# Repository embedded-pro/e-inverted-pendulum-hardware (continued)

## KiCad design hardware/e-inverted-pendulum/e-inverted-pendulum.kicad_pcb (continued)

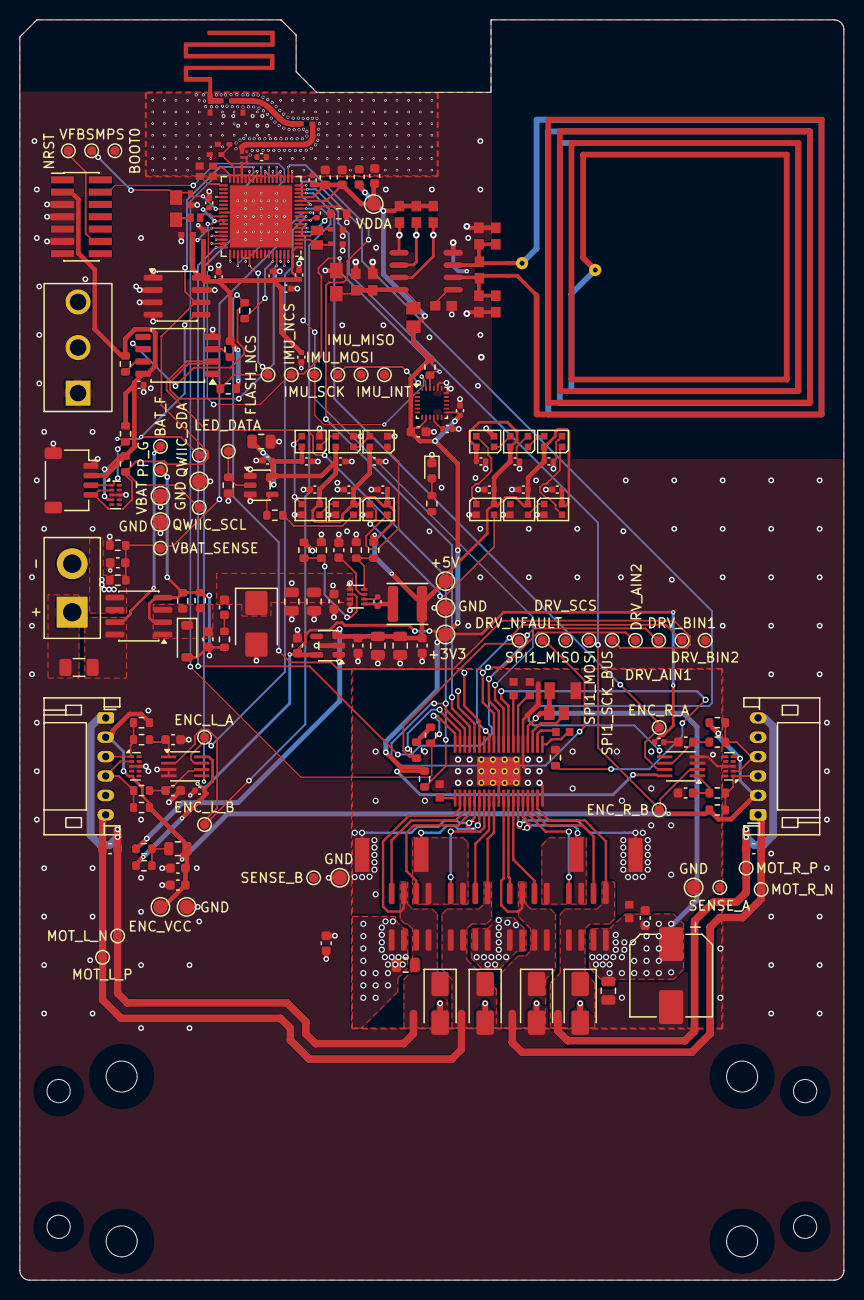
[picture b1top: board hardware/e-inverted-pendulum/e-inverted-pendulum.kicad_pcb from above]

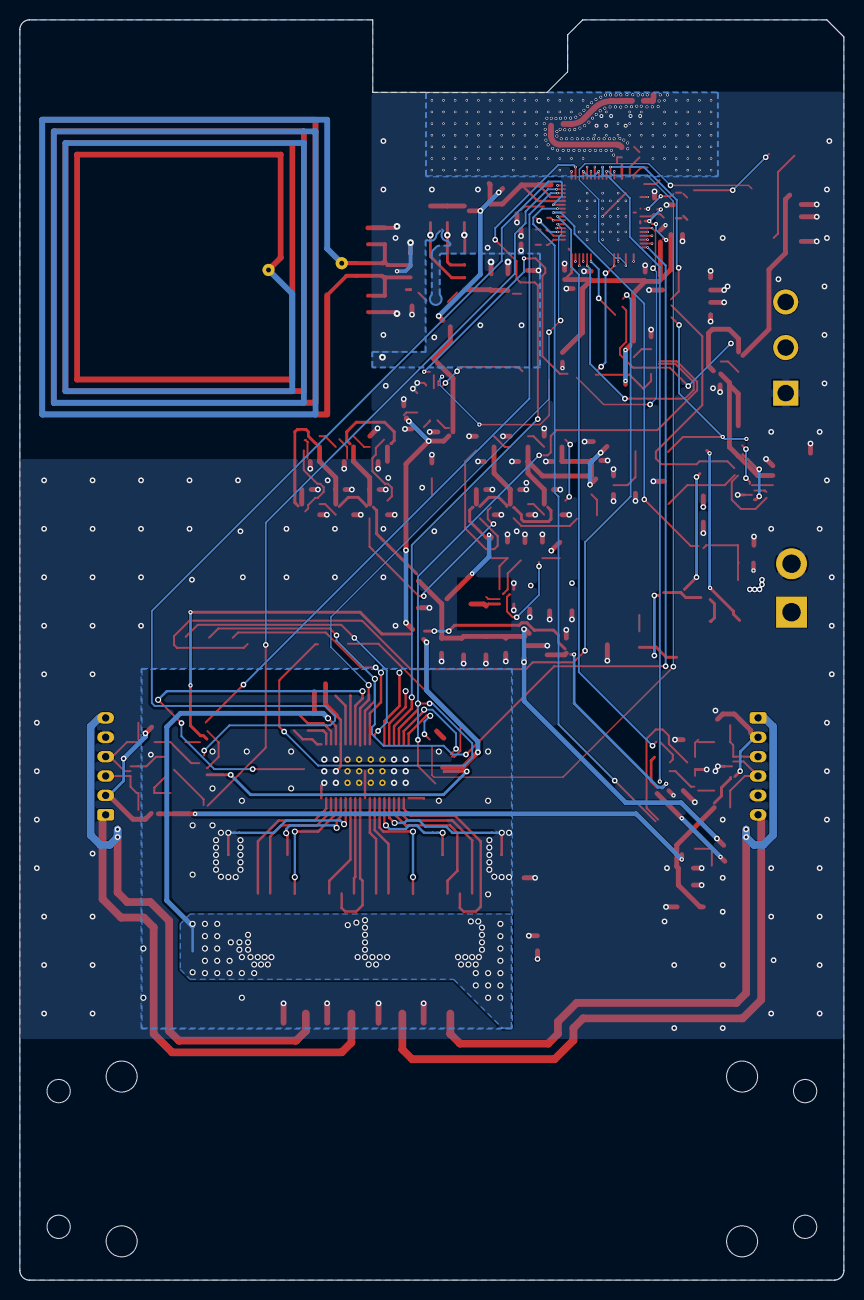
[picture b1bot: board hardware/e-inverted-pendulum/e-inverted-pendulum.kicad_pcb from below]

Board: 4 copper layers, 85.0 x 130.0 mm, 245 parts (4 on the bottom side), 119 nets.

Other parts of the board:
MB1, MB2, MB3, MB4: bracket M3; MountingHole_M3_NPTH_KeepOut7mm
MB5, MB6, MB7, MB8: bracket M2; MountingHole_M2_NPTH_KeepOut5.5mm
MC1, MC2, MC3, MC4: battery cradle; MountingHole_M3_NPTH_KeepOut7mm
MH1: bumper; MountingHole_M3_NPTH_KeepOut7mm
MH2: bumper (nylon); MountingHole_M3_NPTH_KeepOut7mm

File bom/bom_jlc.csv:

Comment,Designator,Footprint,LCSC Part #
MLT-8530,BZ801,Buzzer_MLT-8530_8.5x8.5mm,C94599
47nF 50V,"C101,C205",C_0603_1608Metric,C1622
1uF 50V,"C102,C209,C311,C313,C509,C512",C_0603_1608Metric,C15849
100nF 50V,"C103,C203,C208,C503,C506,C510,C602,C801",C_0603_1608Metric,C14663
10uF 25V,"C201,C202,C502,C505",C_0805_2012Metric,C15850
100nF 16V,"C204,C301,C302,C303,C304,C305,C307,C312,C317,C511,C606,C610,C701,C703,C704,C802,C803",C_0402_1005Metric,C1525
22uF 25V,"C206,C207",C_0805_2012Metric,C45783
2.2uF 25V,C210,C_0603_1608Metric,C23630
4.7uF 10V,"C306,C309,C314",C_0402_1005Metric,C23733
100pF 50V,C308,C_0402_1005Metric,C26409
10nF 50V,"C310,C508,C702",C_0603_1608Metric,C1589
6.8pF 50V,"C315,C316",C_0402_1005Metric,C318598
220u 35V,C507,CP_Elec_8x10,C178562
1nF 50V,C513,C_0402_1005Metric,C307441
10uF 10V,C601,C_0603_1608Metric,C19702
1nF 50V,"C604,C605,C608,C609",C_0603_1608Metric,C1588
BZT52C15,D101,D_SOD-123,C2104
SMBJ15A,D102,D_SMB,C83846
SS34,"D501,D502,D503,D504",D_SMA,C8678
green,D801,LED_0603_1608Metric,C12624
red,D802,LED_0603_1608Metric,C2286
1N4148WS,D803,D_SOD-323,C2128
4A fast,F101,Fuse_1206_3216Metric,C2937379
PTC 100mA,F601,Fuse_0805_2012Metric,C20975
BLM18PG221SN1D,FB301,L_0603_1608Metric,C80165
MLPF-WB55-01E3,FL401,ST_MLPF-WB55-01E3,C2651048
XT30 battery,J101,AMASS_XT30UPB-F_1x02_P5.00mm_Vertical,C108769
STDC14,J301,PinHeader_2x07_P1.27mm_Vertical_SMD,C5307809
"Motor left,Motor right","J601,J602",JST_PH_S6B-PH-K_1x06_P2.00mm_Horizontal,C157920
Qwiic,J801,JST_SH_SM04B-SRSS-TB_1x04-1MP_P1.00mm_Horizontal,C160404
4.7uH,L201,L_Sunlord_SWPA4030S,C57269
10uH,L301,L_0805_2012Metric,C162582
10nH,L302,L_0402_1005Metric,C77103
AO4805,Q101,SOIC-8_3.9x4.9mm_P1.27mm,C3040596
CSD88537ND,"Q501,Q502,Q503,Q504",SOIC-8_3.9x4.9mm_P1.27mm,C117439
MMBT3904,Q801,SOT-23,C20526
100k,"R101,R102,R104",R_0603_1608Metric,C25803
1k,"R103,R303",R_0603_1608Metric,C21190
27k,R105,R_0603_1608Metric,C22967
240k,R201,R_0603_1608Metric,C4197
36k,R202,R_0603_1608Metric,C23147
52.3k,R203,R_0603_1608Metric,C23198
10k,"R204,R302,R515,R516,R518,R701,R702,R703,R704,R803,R807,R810",R_0603_1608Metric,C25804
33,"R301,R805",R_0603_1608Metric,C23140
0,R401,R_0402_1005Metric,C17168
0,"R501,R502,R503,R504,R505,R506,R507,R508,R510,R511,R513,R514,R601",R_0603_1608Metric,C21189
50m,"R509,R512",R_1206_3216Metric,C601102
2.2k,"R517,R808,R809",R_0603_1608Metric,C4190
100,"R604,R606,R608,R610,R804",R_0603_1608Metric,C22775
470,"R801,R806",R_0603_1608Metric,C23179
680,R802,R_0603_1608Metric,C23228
SS-12D10L5,SW101,SW_Slide_SPDT_SS-12D10L5_P4.70mm,C319012
"BOOT0,USER","SW301,SW801",SW_Push_TS-1187A_5.1x5.1mm,C318884
TPS62933F,U201,SOT-583-8,C5219272
TLV75533P,U202,SOT-23-5,C404027
STM32WB55RGV6,U301,QFN-68-1EP_8x8mm_P0.4mm_EP6.4x6.4mm,C401505
DRV8711,U501,HTSSOP-38-1EP_4.4x9.7mm_P0.5mm_EP2.74x4.75mm_ThermalVias,C60013
TPD4E05U06DQAR,"U601,U603,U801",USON-10_2.5x1.0mm_P0.5mm,C138714
SN74LVC3G17DCTR,"U602,U604",SSOP-8_2.95x2.8mm_P0.65mm,C18213
MPU-6500,U701,InvenSense_QFN-24_3x3mm_P0.4mm,C50278
W25Q16JVSSIQ,U702,SOIC-8_5.3x5.3mm_P1.27mm,C131025
M24C64-RMN6TP,U802,SOIC-8_3.9x4.9mm_P1.27mm,C79988
ST25DV04KC-IE8S3,U803,SOIC-8_3.9x4.9mm_P1.27mm,C5221752
32MHz,Y301,Crystal_SMD_2016-4Pin_2.0x1.6mm,C5441424
32.768kHz,Y302,Crystal_SMD_3215-2Pin_3.2x1.5mm,C156244

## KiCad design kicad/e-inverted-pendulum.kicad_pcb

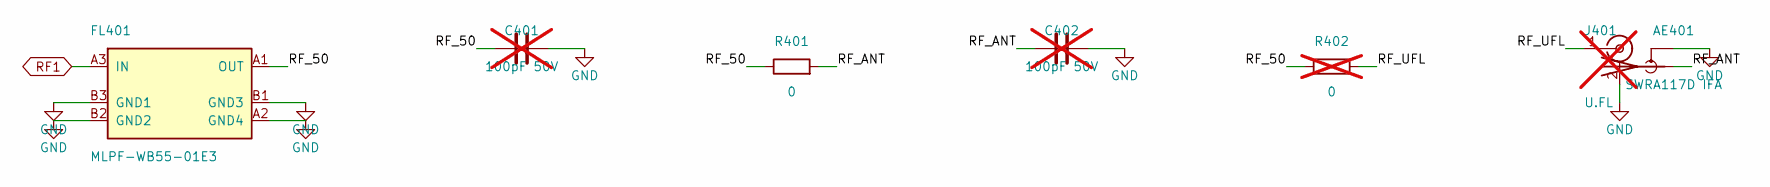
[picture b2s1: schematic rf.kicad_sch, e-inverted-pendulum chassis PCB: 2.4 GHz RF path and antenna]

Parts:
AE401: SWRA117D IFA; Texas_SWRA117D_2.4GHz_Left
C401, C402: 100pF 50V; C_0402_1005Metric; MPN CL05C101JB5NNNC; LCSC C26409; not fitted
FL401: MLPF-WB55-01E3; ST_MLPF-WB55-01E3; MPN MLPF-WB55-01E3; LCSC C2651048
J401: U.FL; U.FL_Hirose_U.FL-R-SMT-1_Vertical; MPN BWU.FL-IPEX1; LCSC C5137195; not fitted
R401: 0; R_0402_1005Metric; MPN 0402WGF0000TCE; LCSC C17168
R402: 0; R_0402_1005Metric; MPN 0402WGF0000TCE; LCSC C17168; not fitted

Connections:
/4 2.4 GHz RF path and antenna/RF_50: C401.1, FL401.A1 (OUT), R401.1, R402.1
/4 2.4 GHz RF path and antenna/RF_ANT: AE401.1 (A), C402.1, R401.2
/4 2.4 GHz RF path and antenna/RF_UFL: J401.1 (In), R402.2
GND: AE401.2 (Shield), C401.2, C402.2, FL401.A2 (GND4), FL401.B1 (GND3), FL401.B2 (GND2), FL401.B3 (GND1), J401.2 (Ext); also elsewhere on the board
RF1: FL401.A3 (IN); also elsewhere on the board

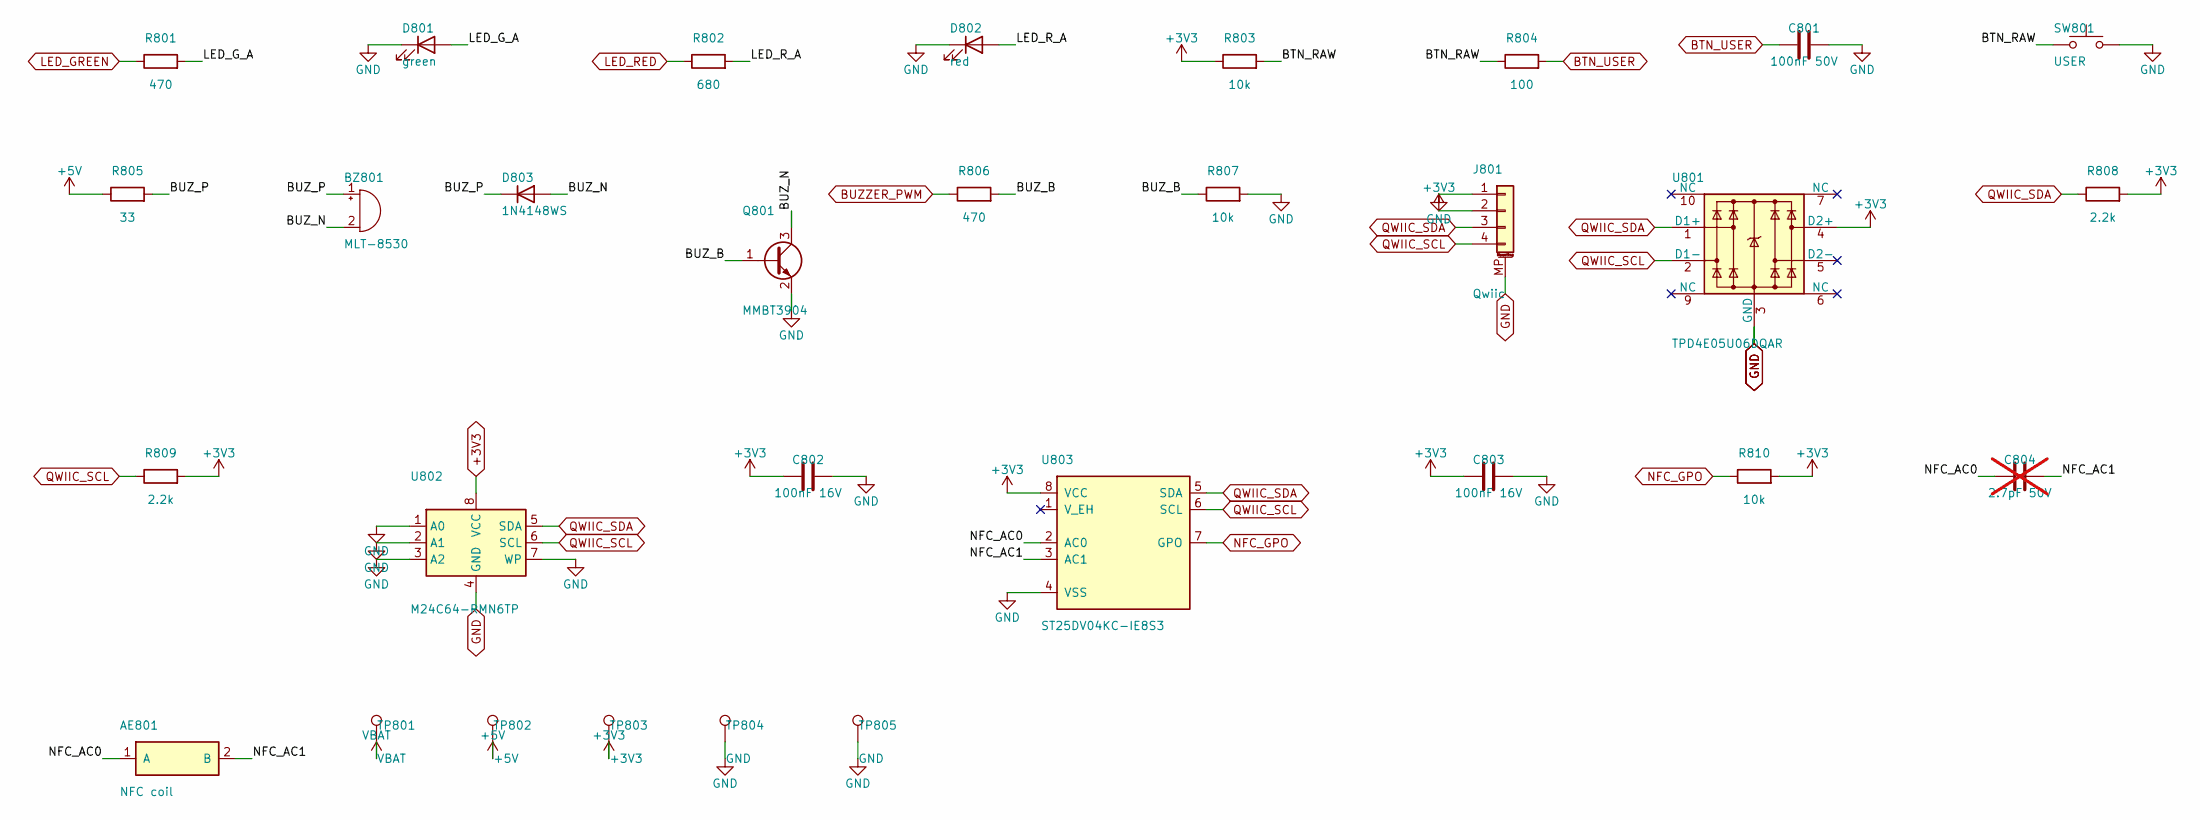
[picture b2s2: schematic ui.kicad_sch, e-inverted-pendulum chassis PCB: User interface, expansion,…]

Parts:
AE801: NFC coil; NFC_Coil_25x21mm
BZ801: MLT-8530; Buzzer_MLT-8530_8.5x8.5mm; MPN MLT-8530; LCSC C94599
C801: 100nF 50V; C_0603_1608Metric; MPN CC0603KRX7R9BB104; LCSC C14663
C802, C803: 100nF 16V; C_0402_1005Metric; MPN CL05B104KO5NNNC; LCSC C1525
C804: 2.7pF 50V; C_0402_1005Metric; MPN CL05C2R7CB5NNNC; LCSC C318593; not fitted
D801: green; LED_0603_1608Metric; MPN KT-0603G; LCSC C12624
D802: red; LED_0603_1608Metric; MPN KT-0603R; LCSC C2286
D803: 1N4148WS; D_SOD-323; MPN 1N4148WS; LCSC C2128
J801: Qwiic; JST_SH_SM04B-SRSS-TB_1x04-1MP_P1.00mm_Horizontal; MPN SM04B-SRSS-TB(LF)(SN); LCSC C160404
Q801: MMBT3904; SOT-23; MPN MMBT3904; LCSC C20526
R801, R806: 470; R_0603_1608Metric; MPN 0603WAF4700T5E; LCSC C23179
R802: 680; R_0603_1608Metric; MPN 0603WAF6800T5E; LCSC C23228
R803, R807, R810: 10k; R_0603_1608Metric; MPN 0603WAF1002T5E; LCSC C25804
R804: 100; R_0603_1608Metric; MPN 0603WAF1000T5E; LCSC C22775
R805: 33; R_0603_1608Metric; MPN 0603WAF330JT5E; LCSC C23140
R808, R809: 2.2k; R_0603_1608Metric; MPN 0603WAF2201T5E; LCSC C4190
SW801: USER; SW_Push_TS-1187A_5.1x5.1mm; MPN TS-1187A-B-A-B; LCSC C318884
TP801: VBAT; TestPoint_Pad_D1.0mm
TP802: +5V; TestPoint_Pad_D1.0mm
TP803: +3V3; TestPoint_Pad_D1.0mm
TP804, TP805: GND; TestPoint_Pad_D1.0mm
U801: TPD4E05U06DQAR; USON-10_2.5x1.0mm_P0.5mm; MPN TPD4E05U06DQAR; LCSC C138714
U802: M24C64-RMN6TP; SOIC-8_3.9x4.9mm_P1.27mm; MPN M24C64-RMN6TP; LCSC C79988
U803: ST25DV04KC-IE8S3; SOIC-8_3.9x4.9mm_P1.27mm; MPN ST25DV04KC-IE8S3; LCSC C5221752

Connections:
+3V3: C802.1, C803.1, J801.2, R803.1, R808.2, R809.2, R810.2, TP803.1, U801.4 (D2+), U802.8 (VCC), U803.8 (VCC); also elsewhere on the board
+5V: R805.1, TP802.1; also elsewhere on the board
/8 User interface, expansion, test points/BTN_RAW: R803.2, R804.1, SW801.1
/8 User interface, expansion, test points/BUZ_B: Q801.1 (B), R806.2, R807.1
/8 User interface, expansion, test points/BUZ_N: BZ801.2 (-), D803.2 (A), Q801.3 (C)
/8 User interface, expansion, test points/BUZ_P: BZ801.1 (+), D803.1 (K), R805.2
/8 User interface, expansion, test points/LED_G_A: D801.2 (A), R801.2
/8 User interface, expansion, test points/LED_R_A: D802.2 (A), R802.2
/8 User interface, expansion, test points/NFC_AC0: AE801.1 (A), C804.1, U803.2 (AC0)
/8 User interface, expansion, test points/NFC_AC1: AE801.2 (B), C804.2, U803.3 (AC1)
BTN_USER: C801.1, R804.2; also elsewhere on the board
BUZZER_PWM: R806.1; also elsewhere on the board
GND: C801.2, C802.2, C803.2, D801.1 (K), D802.1 (K), J801.1, J801.MP (MountPin), Q801.2 (E), R807.2, SW801.2, TP804.1, TP805.1, U801.3 (GND), U801.8 (GND), U802.1 (A0), U802.2 (A1), U802.3 (A2), U802.4 (GND), U802.7 (WP), U803.4 (VSS); also elsewhere on the board
LED_GREEN: R801.1; also elsewhere on the board
LED_RED: R802.1; also elsewhere on the board
NFC_GPO: R810.1, U803.7 (GPO); also elsewhere on the board
QWIIC_SCL: J801.4, R809.1, U801.2 (D1-), U802.6 (SCL), U803.6 (SCL); also elsewhere on the board
QWIIC_SDA: J801.3, R808.1, U801.1 (D1+), U802.5 (SDA), U803.5 (SDA); also elsewhere on the board
VBAT: TP801.1; also elsewhere on the board

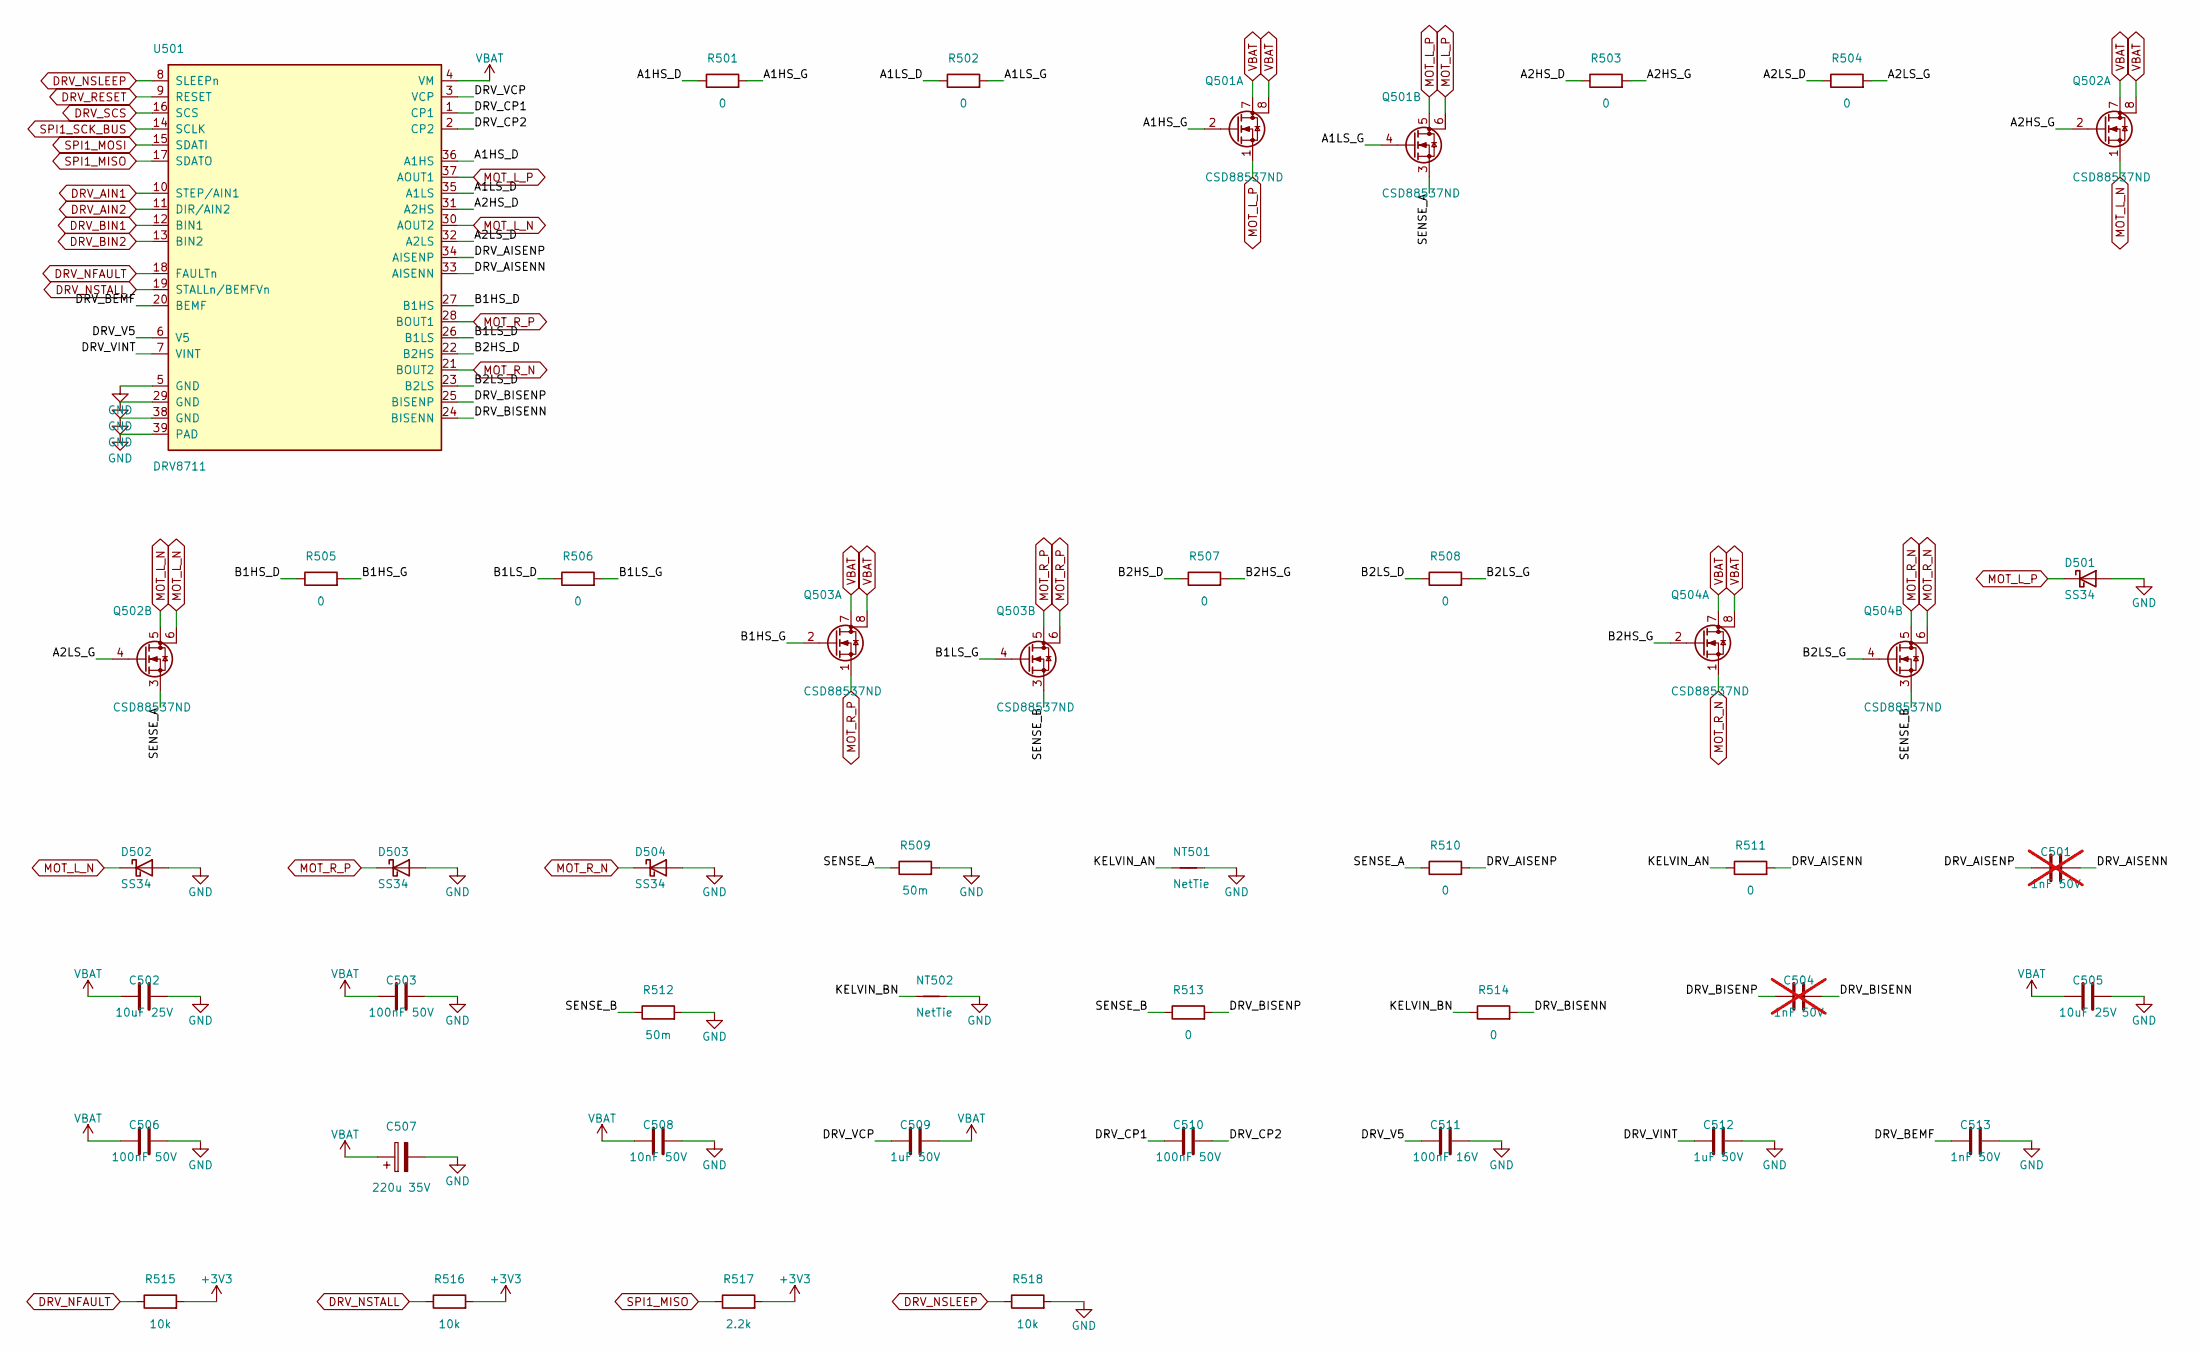
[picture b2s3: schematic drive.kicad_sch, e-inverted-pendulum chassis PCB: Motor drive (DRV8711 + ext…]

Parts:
C501, C504: 1nF 50V; C_0402_1005Metric; MPN CL05C102JB5NNNC; LCSC C307441; not fitted
C502, C505: 10uF 25V; C_0805_2012Metric; MPN CL21A106KAYNNNE; LCSC C15850
C503, C506, C510: 100nF 50V; C_0603_1608Metric; MPN CC0603KRX7R9BB104; LCSC C14663
C507: 220u 35V; CP_Elec_8x10; MPN EEEFK1V221P; LCSC C178562
C508: 10nF 50V; C_0603_1608Metric; MPN CL10B103KB8NNNC; LCSC C1589
C509, C512: 1uF 50V; C_0603_1608Metric; MPN CL10A105KB8NNNC; LCSC C15849
C511: 100nF 16V; C_0402_1005Metric; MPN CL05B104KO5NNNC; LCSC C1525
C513: 1nF 50V; C_0402_1005Metric; MPN CL05C102JB5NNNC; LCSC C307441
D501, D502, D503, D504: SS34; D_SMA; MPN SS34; LCSC C8678
NT501, NT502: NetTie; NetTie-2_SMD_Pad0.5mm
Q501, Q502, Q503, Q504: CSD88537ND; SOIC-8_3.9x4.9mm_P1.27mm; MPN CSD88537ND; LCSC C117439
R501, R502, R503, R504, R505, R506, R507, R508, R510, R511, R513, R514: 0; R_0603_1608Metric; MPN 0603WAF0000T5E; LCSC C21189
R509, R512: 50m; R_1206_3216Metric; MPN HoLR1206-1W-50mR-1%-75ppm; LCSC C601102
R515, R516, R518: 10k; R_0603_1608Metric; MPN 0603WAF1002T5E; LCSC C25804
R517: 2.2k; R_0603_1608Metric; MPN 0603WAF2201T5E; LCSC C4190
U501: DRV8711; HTSSOP-38-1EP_4.4x9.7mm_P0.5mm_EP2.74x4.75mm_ThermalVias; MPN DRV8711DCPR; LCSC C60013

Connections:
+3V3: R515.2, R516.2, R517.2; also elsewhere on the board
/5 Motor drive (DRV8711 + external FETs)/A1HS_D: R501.1, U501.36 (A1HS)
/5 Motor drive (DRV8711 + external FETs)/A1HS_G: Q501.2 (G), R501.2
/5 Motor drive (DRV8711 + external FETs)/A1LS_D: R502.1, U501.35 (A1LS)
/5 Motor drive (DRV8711 + external FETs)/A1LS_G: Q501.4 (G), R502.2
/5 Motor drive (DRV8711 + external FETs)/A2HS_D: R503.1, U501.31 (A2HS)
/5 Motor drive (DRV8711 + external FETs)/A2HS_G: Q502.2 (G), R503.2
/5 Motor drive (DRV8711 + external FETs)/A2LS_D: R504.1, U501.32 (A2LS)
/5 Motor drive (DRV8711 + external FETs)/A2LS_G: Q502.4 (G), R504.2
/5 Motor drive (DRV8711 + external FETs)/B1HS_D: R505.1, U501.27 (B1HS)
/5 Motor drive (DRV8711 + external FETs)/B1HS_G: Q503.2 (G), R505.2
/5 Motor drive (DRV8711 + external FETs)/B1LS_D: R506.1, U501.26 (B1LS)
/5 Motor drive (DRV8711 + external FETs)/B1LS_G: Q503.4 (G), R506.2
/5 Motor drive (DRV8711 + external FETs)/B2HS_D: R507.1, U501.22 (B2HS)
/5 Motor drive (DRV8711 + external FETs)/B2HS_G: Q504.2 (G), R507.2
/5 Motor drive (DRV8711 + external FETs)/B2LS_D: R508.1, U501.23 (B2LS)
/5 Motor drive (DRV8711 + external FETs)/B2LS_G: Q504.4 (G), R508.2
/5 Motor drive (DRV8711 + external FETs)/DRV_AISENN: C501.2, R511.2, U501.33 (AISENN)
/5 Motor drive (DRV8711 + external FETs)/DRV_AISENP: C501.1, R510.2, U501.34 (AISENP)
/5 Motor drive (DRV8711 + external FETs)/DRV_BEMF: C513.1, U501.20 (BEMF)
/5 Motor drive (DRV8711 + external FETs)/DRV_BISENN: C504.2, R514.2, U501.24 (BISENN)
/5 Motor drive (DRV8711 + external FETs)/DRV_BISENP: C504.1, R513.2, U501.25 (BISENP)
/5 Motor drive (DRV8711 + external FETs)/DRV_CP1: C510.1, U501.1 (CP1)
/5 Motor drive (DRV8711 + external FETs)/DRV_CP2: C510.2, U501.2 (CP2)
/5 Motor drive (DRV8711 + external FETs)/DRV_V5: C511.1, U501.6 (V5)
/5 Motor drive (DRV8711 + external FETs)/DRV_VCP: C509.1, U501.3 (VCP)
/5 Motor drive (DRV8711 + external FETs)/DRV_VINT: C512.1, U501.7 (VINT)
/5 Motor drive (DRV8711 + external FETs)/KELVIN_AN: NT501.1, R511.1
/5 Motor drive (DRV8711 + external FETs)/KELVIN_BN: NT502.1, R514.1
/5 Motor drive (DRV8711 + external FETs)/SENSE_A: Q501.3 (S), Q502.3 (S), R509.1, R510.1
/5 Motor drive (DRV8711 + external FETs)/SENSE_B: Q503.3 (S), Q504.3 (S), R512.1, R513.1
DRV_AIN1: U501.10 (STEP/AIN1); also elsewhere on the board
DRV_AIN2: U501.11 (DIR/AIN2); also elsewhere on the board
DRV_BIN1: U501.12 (BIN1); also elsewhere on the board
DRV_BIN2: U501.13 (BIN2); also elsewhere on the board
DRV_NFAULT: R515.1, U501.18 (FAULTn); also elsewhere on the board
DRV_NSLEEP: R518.1, U501.8 (SLEEPn); also elsewhere on the board
DRV_NSTALL: R516.1, U501.19 (STALLn/BEMFVn); also elsewhere on the board
DRV_RESET: U501.9 (RESET); also elsewhere on the board
DRV_SCS: U501.16 (SCS); also elsewhere on the board
GND: C502.2, C503.2, C505.2, C506.2, C507.2, C508.2, C511.2, C512.2, C513.2, D501.2 (A), D502.2 (A), D503.2 (A), D504.2 (A), NT501.2, NT502.2, R509.2, R512.2, R518.2, U501.5 (GND), U501.29 (GND), U501.38 (GND), U501.39 (PAD); also elsewhere on the board
MOT_L_N: D502.1 (K), Q502.1 (S), Q502.5 (D), Q502.6 (D), U501.30 (AOUT2); also elsewhere on the board
MOT_L_P: D501.1 (K), Q501.1 (S), Q501.5 (D), Q501.6 (D), U501.37 (AOUT1); also elsewhere on the board
MOT_R_N: D504.1 (K), Q504.1 (S), Q504.5 (D), Q504.6 (D), U501.21 (BOUT2); also elsewhere on the board
MOT_R_P: D503.1 (K), Q503.1 (S), Q503.5 (D), Q503.6 (D), U501.28 (BOUT1); also elsewhere on the board
SPI1_MISO: R517.1, U501.17 (SDATO); also elsewhere on the board
SPI1_MOSI: U501.15 (SDATI); also elsewhere on the board
SPI1_SCK_BUS: U501.14 (SCLK); also elsewhere on the board
VBAT: C502.1, C503.1, C505.1, C506.1, C507.1, C508.1, C509.2, Q501.7 (D), Q501.8 (D), Q502.7 (D), Q502.8 (D), Q503.7 (D), Q503.8 (D), Q504.7 (D), Q504.8 (D), U501.4 (VM); also elsewhere on the board

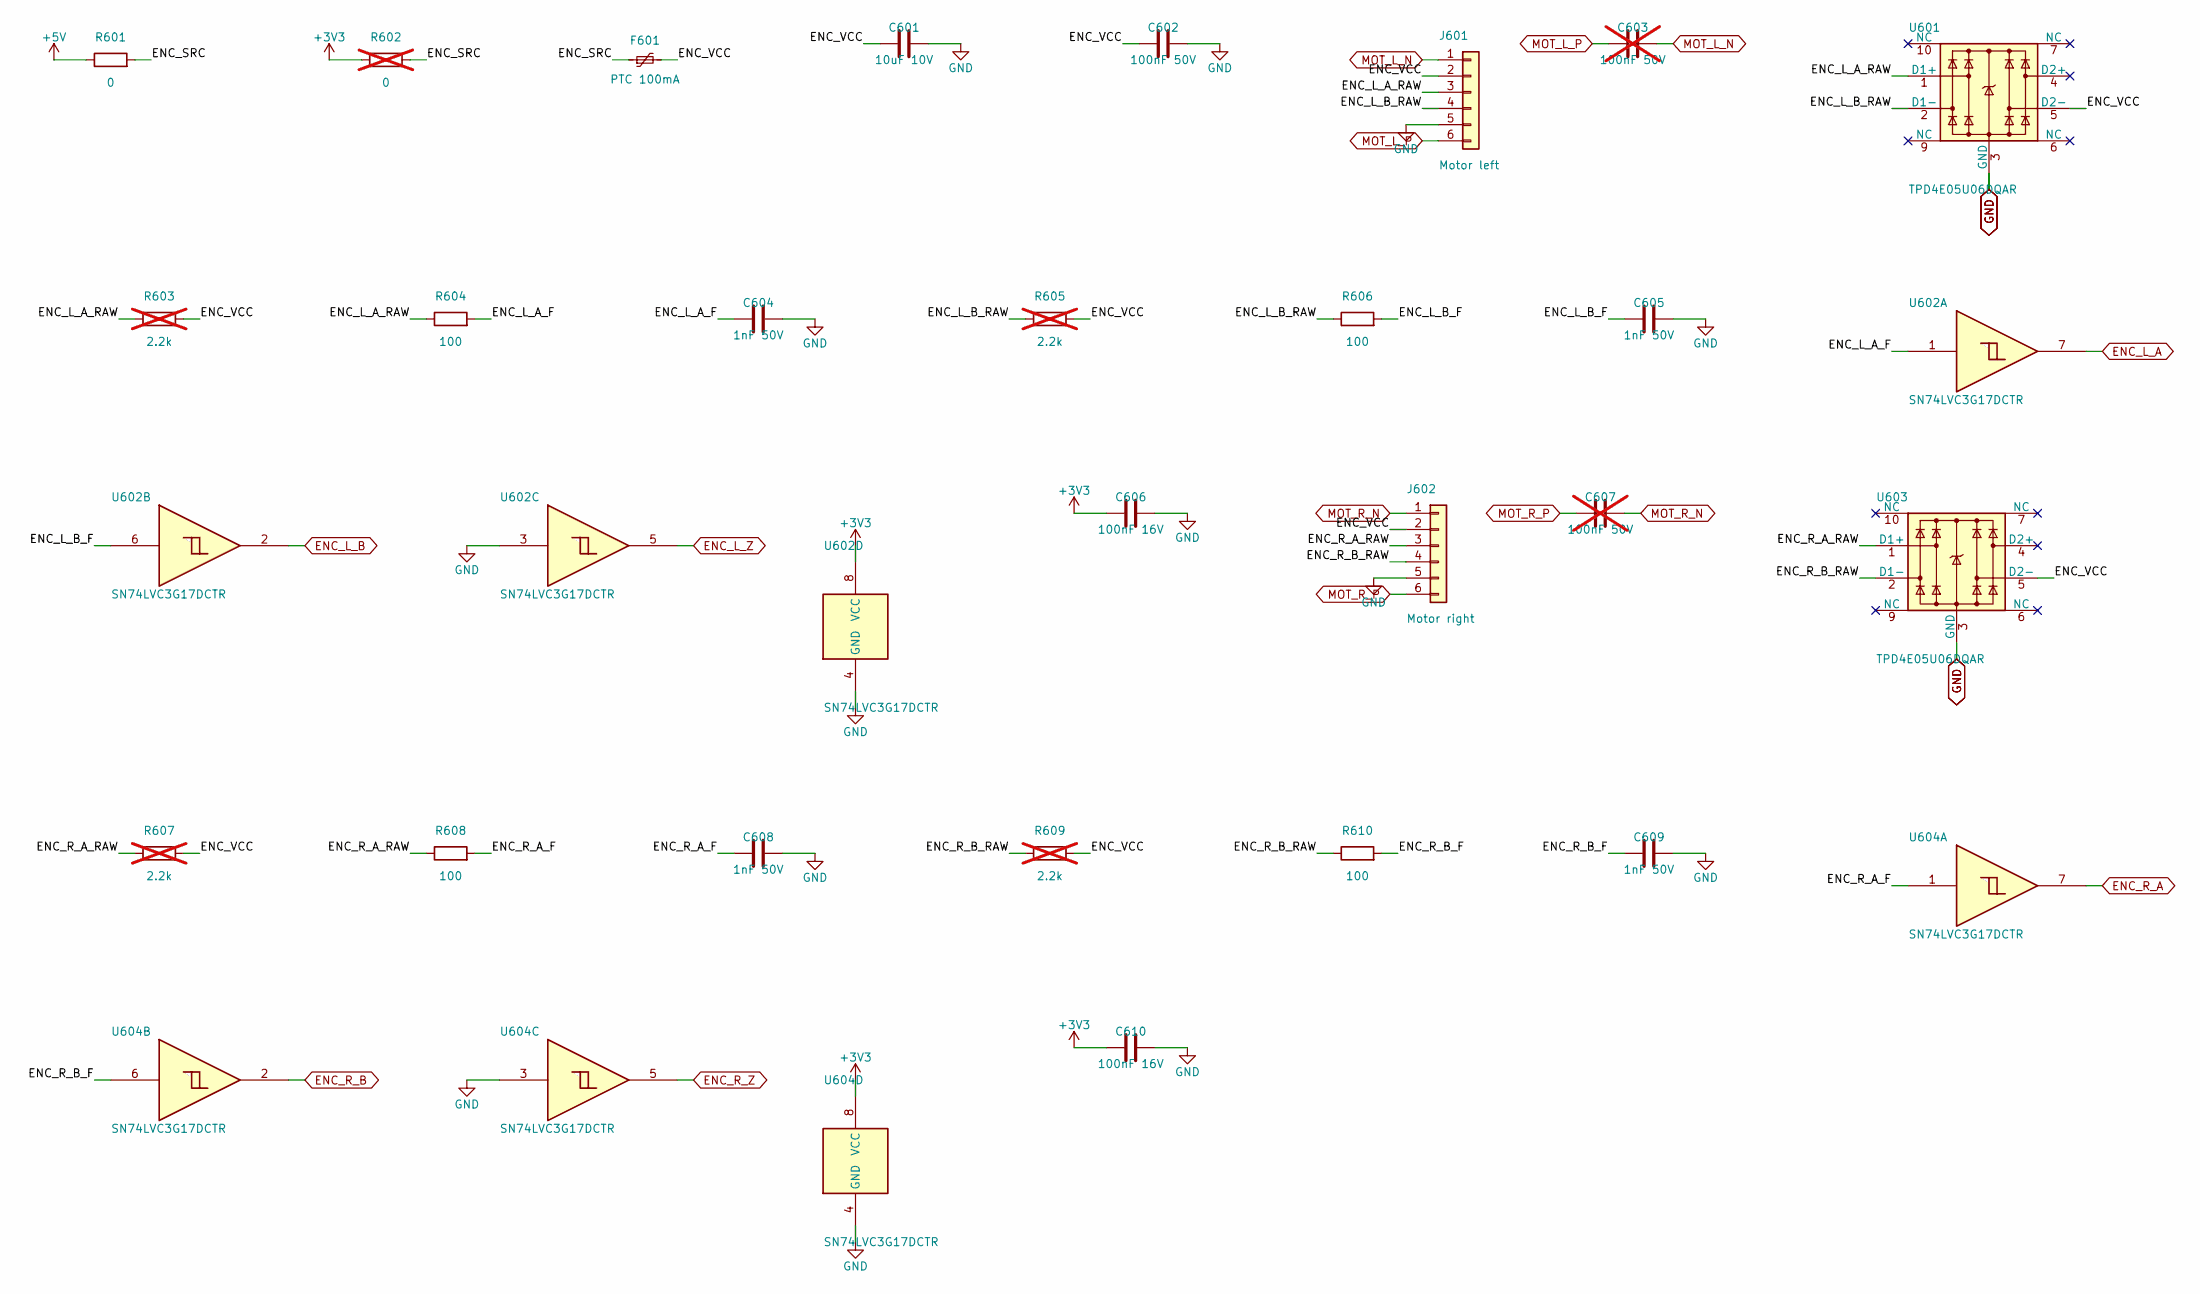
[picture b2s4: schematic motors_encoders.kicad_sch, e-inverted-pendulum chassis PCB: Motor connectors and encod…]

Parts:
C601: 10uF 10V; C_0603_1608Metric; MPN CL10A106KP8NNNC; LCSC C19702
C602: 100nF 50V; C_0603_1608Metric; MPN CC0603KRX7R9BB104; LCSC C14663
C603, C607: 100nF 50V; C_0603_1608Metric; MPN CC0603KRX7R9BB104; LCSC C14663; not fitted
C604, C605, C608, C609: 1nF 50V; C_0603_1608Metric; MPN CL10B102KB8NNNC; LCSC C1588
C606, C610: 100nF 16V; C_0402_1005Metric; MPN CL05B104KO5NNNC; LCSC C1525
F601: PTC 100mA; Fuse_0805_2012Metric; MPN SMD0805P010TF; LCSC C20975
J601: Motor left; JST_PH_S6B-PH-K_1x06_P2.00mm_Horizontal; MPN S6B-PH-K-S(LF)(SN); LCSC C157920
J602: Motor right; JST_PH_S6B-PH-K_1x06_P2.00mm_Horizontal; MPN S6B-PH-K-S(LF)(SN); LCSC C157920
R601: 0; R_0603_1608Metric; MPN 0603WAF0000T5E; LCSC C21189
R602: 0; R_0603_1608Metric; MPN 0603WAF0000T5E; LCSC C21189; not fitted
R603, R605, R607, R609: 2.2k; R_0603_1608Metric; MPN 0603WAF2201T5E; LCSC C4190; not fitted
R604, R606, R608, R610: 100; R_0603_1608Metric; MPN 0603WAF1000T5E; LCSC C22775
U601, U603: TPD4E05U06DQAR; USON-10_2.5x1.0mm_P0.5mm; MPN TPD4E05U06DQAR; LCSC C138714
U602, U604: SN74LVC3G17DCTR; SSOP-8_2.95x2.8mm_P0.65mm; MPN SN74LVC3G17DCTR; LCSC C18213

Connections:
+3V3: C606.1, C610.1, R602.1, U602.8 (VCC), U604.8 (VCC); also elsewhere on the board
+5V: R601.1; also elsewhere on the board
/6 Motor connectors and encoder inputs/ENC_L_A_F: C604.1, R604.2, U602.1
/6 Motor connectors and encoder inputs/ENC_L_A_RAW: J601.3, R603.1, R604.1, U601.1 (D1+)
/6 Motor connectors and encoder inputs/ENC_L_B_F: C605.1, R606.2, U602.6
/6 Motor connectors and encoder inputs/ENC_L_B_RAW: J601.4, R605.1, R606.1, U601.2 (D1-)
/6 Motor connectors and encoder inputs/ENC_R_A_F: C608.1, R608.2, U604.1
/6 Motor connectors and encoder inputs/ENC_R_A_RAW: J602.3, R607.1, R608.1, U603.1 (D1+)
/6 Motor connectors and encoder inputs/ENC_R_B_F: C609.1, R610.2, U604.6
/6 Motor connectors and encoder inputs/ENC_R_B_RAW: J602.4, R609.1, R610.1, U603.2 (D1-)
/6 Motor connectors and encoder inputs/ENC_SRC: F601.1, R601.2, R602.2
/6 Motor connectors and encoder inputs/ENC_VCC: C601.1, C602.1, F601.2, J601.2, J602.2, R603.2, R605.2, R607.2, R609.2, U601.5 (D2-), U603.5 (D2-)
ENC_L_A: U602.7; also elsewhere on the board
ENC_L_B: U602.2; also elsewhere on the board
ENC_L_Z: U602.5; also elsewhere on the board
ENC_R_A: U604.7; also elsewhere on the board
ENC_R_B: U604.2; also elsewhere on the board
ENC_R_Z: U604.5; also elsewhere on the board
GND: C601.2, C602.2, C604.2, C605.2, C606.2, C608.2, C609.2, C610.2, J601.5, J602.5, U601.3 (GND), U601.8 (GND), U602.3, U602.4 (GND), U603.3 (GND), U603.8 (GND), U604.3, U604.4 (GND); also elsewhere on the board
MOT_L_N: C603.2, J601.1; also elsewhere on the board
MOT_L_P: C603.1, J601.6; also elsewhere on the board
MOT_R_N: C607.2, J602.1; also elsewhere on the board
MOT_R_P: C607.1, J602.6; also elsewhere on the board

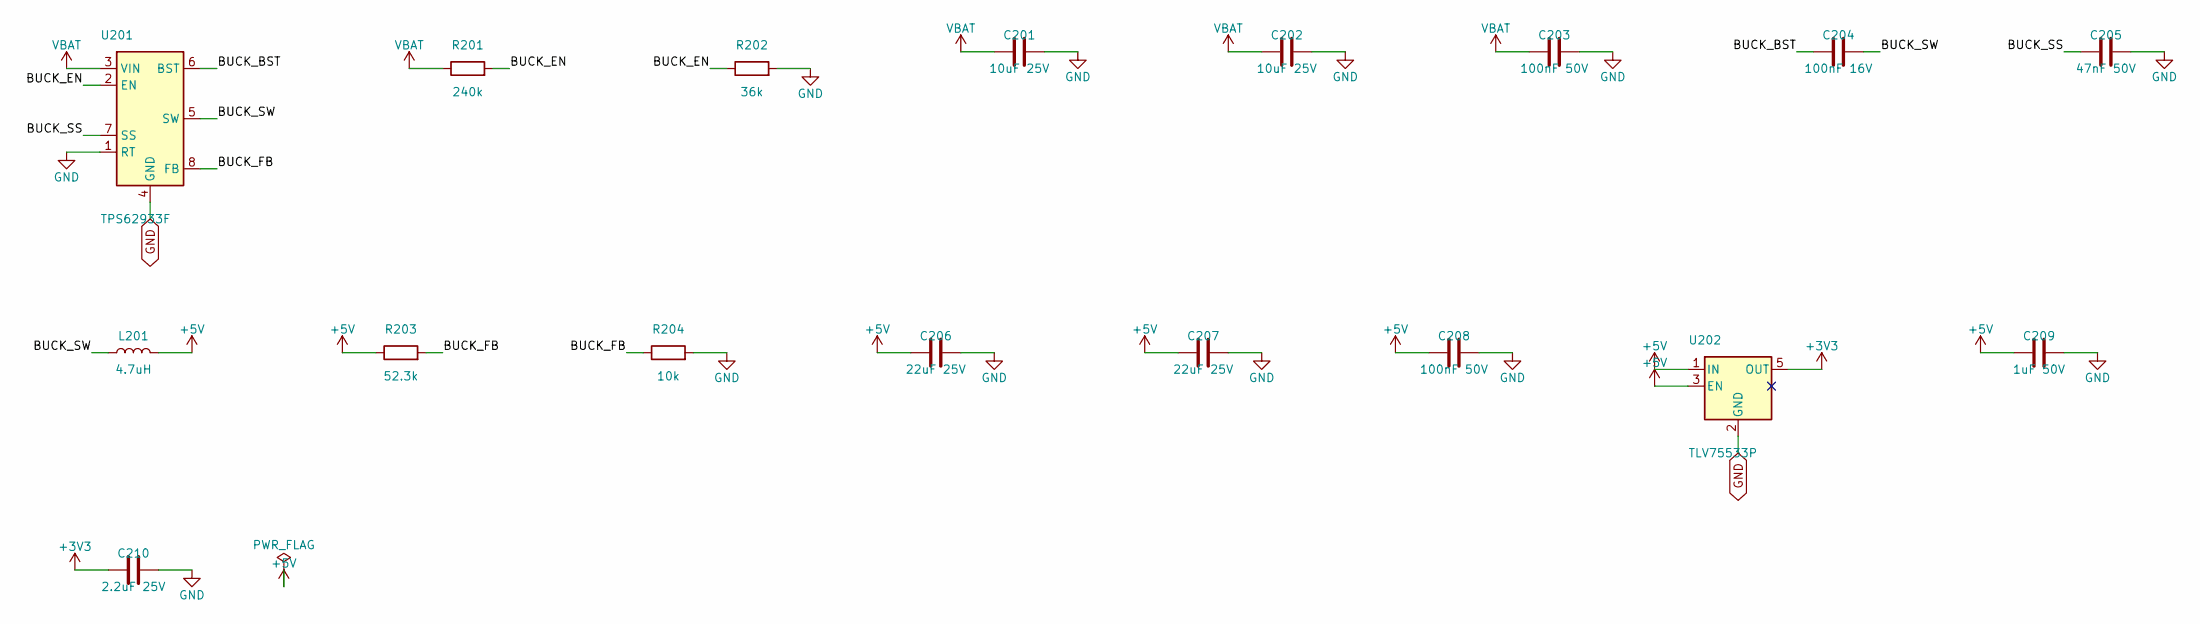
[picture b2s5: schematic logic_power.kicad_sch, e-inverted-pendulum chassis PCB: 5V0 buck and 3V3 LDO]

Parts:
C201, C202: 10uF 25V; C_0805_2012Metric; MPN CL21A106KAYNNNE; LCSC C15850
C203, C208: 100nF 50V; C_0603_1608Metric; MPN CC0603KRX7R9BB104; LCSC C14663
C204: 100nF 16V; C_0402_1005Metric; MPN CL05B104KO5NNNC; LCSC C1525
C205: 47nF 50V; C_0603_1608Metric; MPN CL10B473KB8NNNC; LCSC C1622
C206, C207: 22uF 25V; C_0805_2012Metric; MPN CL21A226MAQNNNE; LCSC C45783
C209: 1uF 50V; C_0603_1608Metric; MPN CL10A105KB8NNNC; LCSC C15849
C210: 2.2uF 25V; C_0603_1608Metric; MPN CL10A225KO8NNNC; LCSC C23630
L201: 4.7uH; L_Sunlord_SWPA4030S; MPN SWPA4030S4R7MT; LCSC C57269
R201: 240k; R_0603_1608Metric; MPN 0603WAF2403T5E; LCSC C4197
R202: 36k; R_0603_1608Metric; MPN 0603WAF3602T5E; LCSC C23147
R203: 52.3k; R_0603_1608Metric; MPN 0603WAF5232T5E; LCSC C23198
R204: 10k; R_0603_1608Metric; MPN 0603WAF1002T5E; LCSC C25804
U201: TPS62933F; SOT-583-8; MPN TPS62933FDRLR; LCSC C5219272
U202: TLV75533P; SOT-23-5; MPN TLV75533PDBVR; LCSC C404027

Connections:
+3V3: C210.1, U202.5 (OUT); also elsewhere on the board
+5V: C206.1, C207.1, C208.1, C209.1, L201.2, R203.1, U202.1 (IN), U202.3 (EN); also elsewhere on the board
/2 5V0 buck and 3V3 LDO/BUCK_BST: C204.1, U201.6 (BST)
/2 5V0 buck and 3V3 LDO/BUCK_EN: R201.2, R202.1, U201.2 (EN)
/2 5V0 buck and 3V3 LDO/BUCK_FB: R203.2, R204.1, U201.8 (FB)
/2 5V0 buck and 3V3 LDO/BUCK_SS: C205.1, U201.7 (SS)
/2 5V0 buck and 3V3 LDO/BUCK_SW: C204.2, L201.1, U201.5 (SW)
GND: C201.2, C202.2, C203.2, C205.2, C206.2, C207.2, C208.2, C209.2, C210.2, R202.2, R204.2, U201.1 (RT), U201.4 (GND), U202.2 (GND); also elsewhere on the board
VBAT: C201.1, C202.1, C203.1, R201.1, U201.3 (VIN); also elsewhere on the board
